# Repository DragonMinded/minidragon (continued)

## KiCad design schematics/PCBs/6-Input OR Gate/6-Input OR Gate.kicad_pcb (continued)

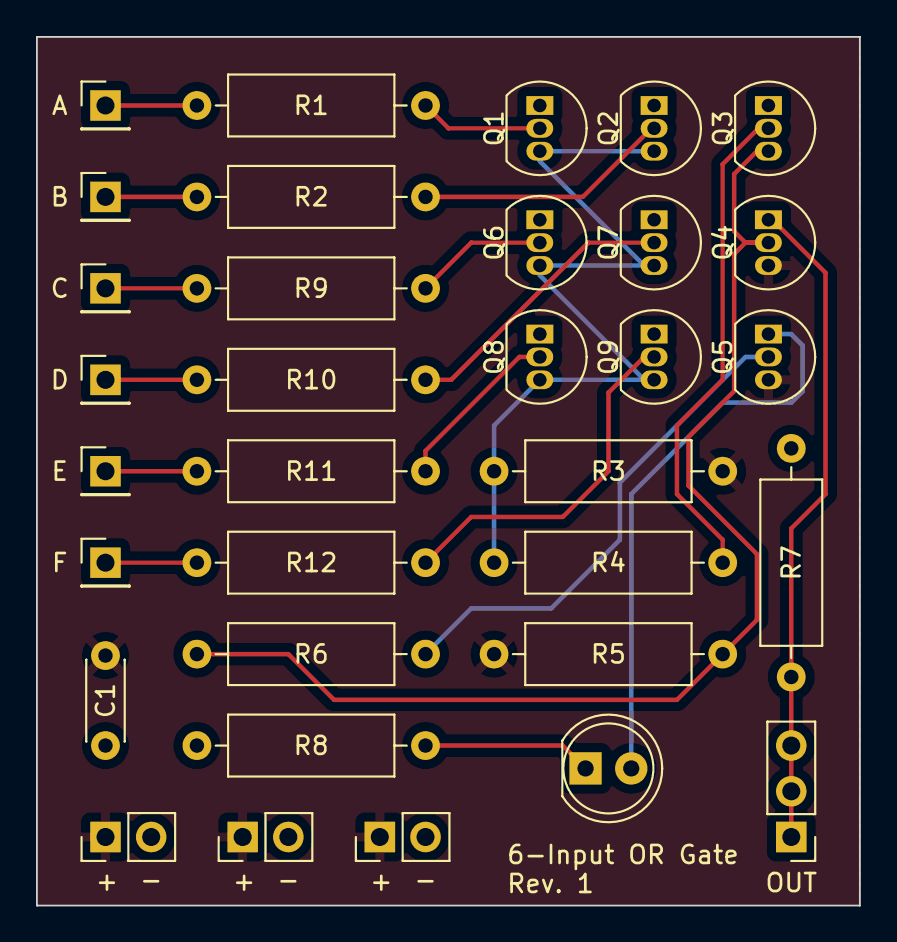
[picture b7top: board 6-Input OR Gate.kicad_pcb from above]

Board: 2 copper layers, 45.7 x 48.3 mm, 33 parts (0 on the bottom side), 21 nets.

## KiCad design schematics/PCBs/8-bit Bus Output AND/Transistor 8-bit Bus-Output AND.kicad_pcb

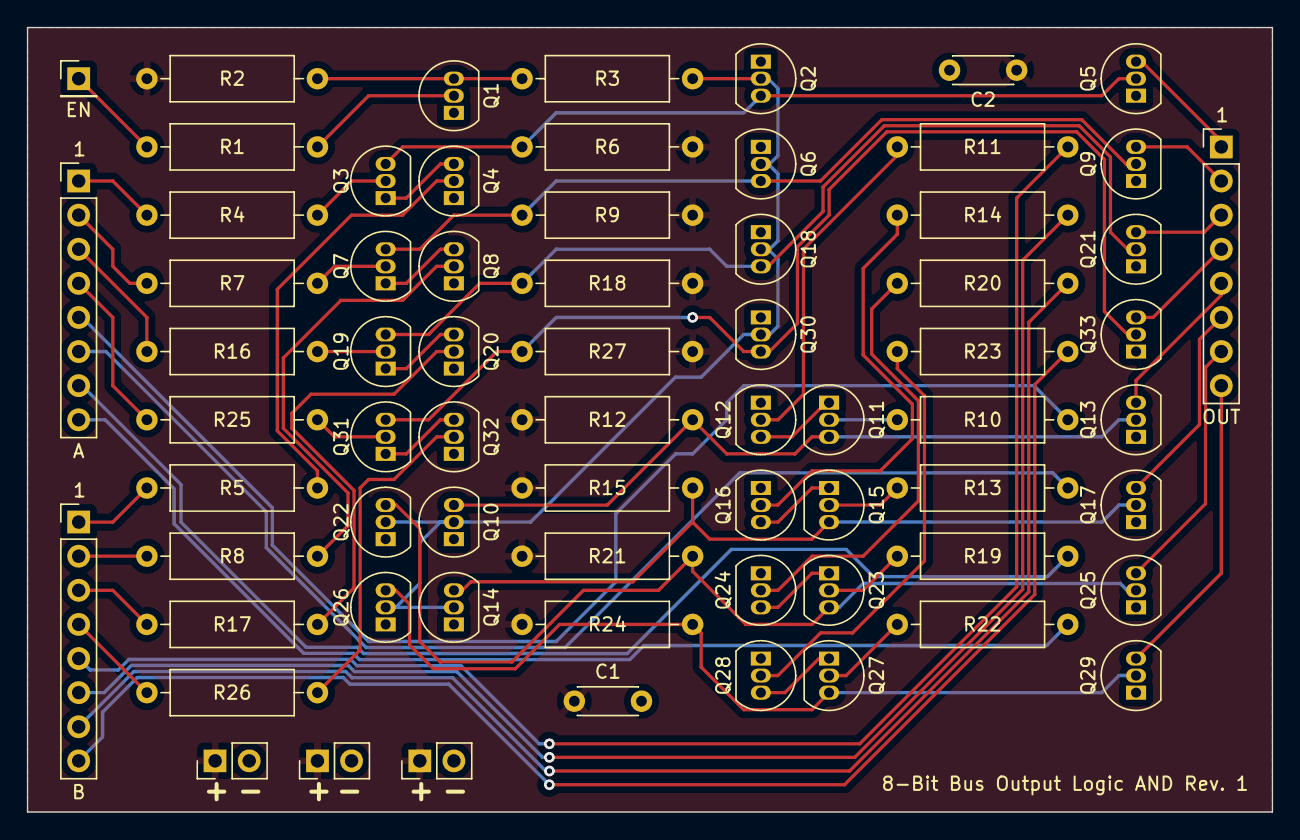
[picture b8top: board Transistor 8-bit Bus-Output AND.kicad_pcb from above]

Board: 2 copper layers, 92.7 x 58.4 mm, 69 parts (0 on the bottom side), 62 nets.

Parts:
C1, C2: 0.1uF; C_Disc_D4.3mm_W1.9mm_P5.00mm
J1: EN; PinHeader_1x01_P2.54mm_Vertical
J2, J3, J4: POWER; PinHeader_1x02_P2.54mm_Vertical
J5: A; PinHeader_1x08_P2.54mm_Vertical
J6: B; PinHeader_1x08_P2.54mm_Vertical
J7: OUT; PinHeader_1x08_P2.54mm_Vertical
Q1, Q2, Q3, Q4, Q5, Q6, Q7, Q8, Q9, Q10, Q11, Q12, Q13, Q14, Q15, Q16, Q17, Q18, Q19, Q20, Q21, Q22, Q23, Q24, Q25, Q26, Q27, Q28, Q29, Q30, Q31, Q32, Q33: 2N2222; TO-92_Inline
R1, R4, R5, R7, R8, R10, R11, R13, R14, R16, R17, R19, R20, R22, R23, R25, R26: 10K; R_Axial_DIN0309_L9.0mm_D3.2mm_P12.70mm_Horizontal
R2, R6, R9, R12, R15, R18, R21, R24, R27: 1K; R_Axial_DIN0309_L9.0mm_D3.2mm_P12.70mm_Horizontal
R3: 100; R_Axial_DIN0309_L9.0mm_D3.2mm_P12.70mm_Horizontal

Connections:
/A1: J5.1, R4.2
/A2: J5.2, R7.2
/A3: J5.3, R16.2
/A4: J5.4, R25.2
/A5: J5.5, R10.2
/A6: J5.6, R13.2
/A7: J5.7, R19.2
/A8: J5.8, R22.2
/B1: J6.1, R5.2
/B2: J6.2, R8.2
/B3: J6.3, R17.2
/B4: J6.4, R26.2
/B5: J6.5, R11.2
/B6: J6.6, R14.2
/B7: J6.7, R20.2
/B8: J6.8, R23.2
/EN_INT: Q2.2 (B), Q6.2 (B), Q10.2 (B), Q14.2 (B), Q18.2 (B), Q22.2 (B), Q26.2 (B), Q30.2 (B), R3.1
/O1: J7.1, Q5.3 (C)
/O2: J7.2, Q9.3 (C)
/O3: J7.3, Q21.3 (C)
/O4: J7.4, Q33.3 (C)
/O5: J7.5, Q13.3 (C)
/O6: J7.6, Q17.3 (C)
/O7: J7.7, Q25.3 (C)
/O8: J7.8, Q29.3 (C)
GND: C1.2, C2.2, J2.2, J3.2, J4.2, Q1.1 (E), Q2.1 (E), Q4.1 (E), Q5.1 (E), Q6.1 (E), Q8.1 (E), Q9.1 (E), Q10.1 (E), Q12.1 (E), Q13.1 (E), Q14.1 (E), Q16.1 (E), Q17.1 (E), Q18.1 (E), Q20.1 (E), Q21.1 (E), Q22.1 (E), Q24.1 (E), Q25.1 (E), Q26.1 (E), Q28.1 (E), Q29.1 (E), Q30.1 (E), Q32.1 (E), Q33.1 (E)
unnamed: J1.1, R1.2
unnamed: Q1.2 (B), R1.1
unnamed: Q1.3 (C), R2.1, R3.2
unnamed: Q2.3 (C), Q3.3 (C), Q5.2 (B), R6.1
unnamed: Q3.2 (B), R4.1
unnamed: Q3.1 (E), Q4.3 (C)
unnamed: Q4.2 (B), R5.1
unnamed: Q6.3 (C), Q7.3 (C), Q9.2 (B), R9.1
unnamed: Q7.2 (B), R7.1
unnamed: Q7.1 (E), Q8.3 (C)
unnamed: Q8.2 (B), R8.1
unnamed: Q10.3 (C), Q11.3 (C), Q13.2 (B), R12.1
unnamed: Q11.2 (B), R10.1
unnamed: Q11.1 (E), Q12.3 (C)
unnamed: Q12.2 (B), R11.1
unnamed: Q14.3 (C), Q15.3 (C), Q17.2 (B), R15.1
unnamed: Q15.2 (B), R13.1
unnamed: Q15.1 (E), Q16.3 (C)
unnamed: Q16.2 (B), R14.1
unnamed: Q18.3 (C), Q19.3 (C), Q21.2 (B), R18.1
unnamed: Q19.2 (B), R16.1
unnamed: Q19.1 (E), Q20.3 (C)
unnamed: Q20.2 (B), R17.1
unnamed: Q22.3 (C), Q23.3 (C), Q25.2 (B), R21.1
unnamed: Q23.2 (B), R19.1
unnamed: Q23.1 (E), Q24.3 (C)
unnamed: Q24.2 (B), R20.1
unnamed: Q26.3 (C), Q27.3 (C), Q29.2 (B), R24.1
unnamed: Q27.2 (B), R22.1
unnamed: Q27.1 (E), Q28.3 (C)
unnamed: Q28.2 (B), R23.1
unnamed: Q30.3 (C), Q31.3 (C), Q33.2 (B), R27.1
unnamed: Q31.2 (B), R25.1
unnamed: Q31.1 (E), Q32.3 (C)
unnamed: Q32.2 (B), R26.1
VCC: C1.1, C2.1, J2.1, J3.1, J4.1, R2.2, R6.2, R9.2, R12.2, R15.2, R18.2, R21.2, R24.2, R27.2
